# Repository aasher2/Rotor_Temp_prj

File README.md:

# Welcome!

We created this repository in case another team is tasked to bring this project to completion. All necessary documents and many useful links are provided.

To download this entire project as a zipped folder, simply click the "Clone or Download" drop-down to the right of the home page. The option to download as a zipped folder will then be presented. 

This repository is split between paths for firmware and hardware. The firmware path just leads to the final code used for the BLE server and BLE client. The hardware path diverges into paths for the final design and for the proof of concept design. Most of the documents/datasheets/references will be found in the proof of concept folder.

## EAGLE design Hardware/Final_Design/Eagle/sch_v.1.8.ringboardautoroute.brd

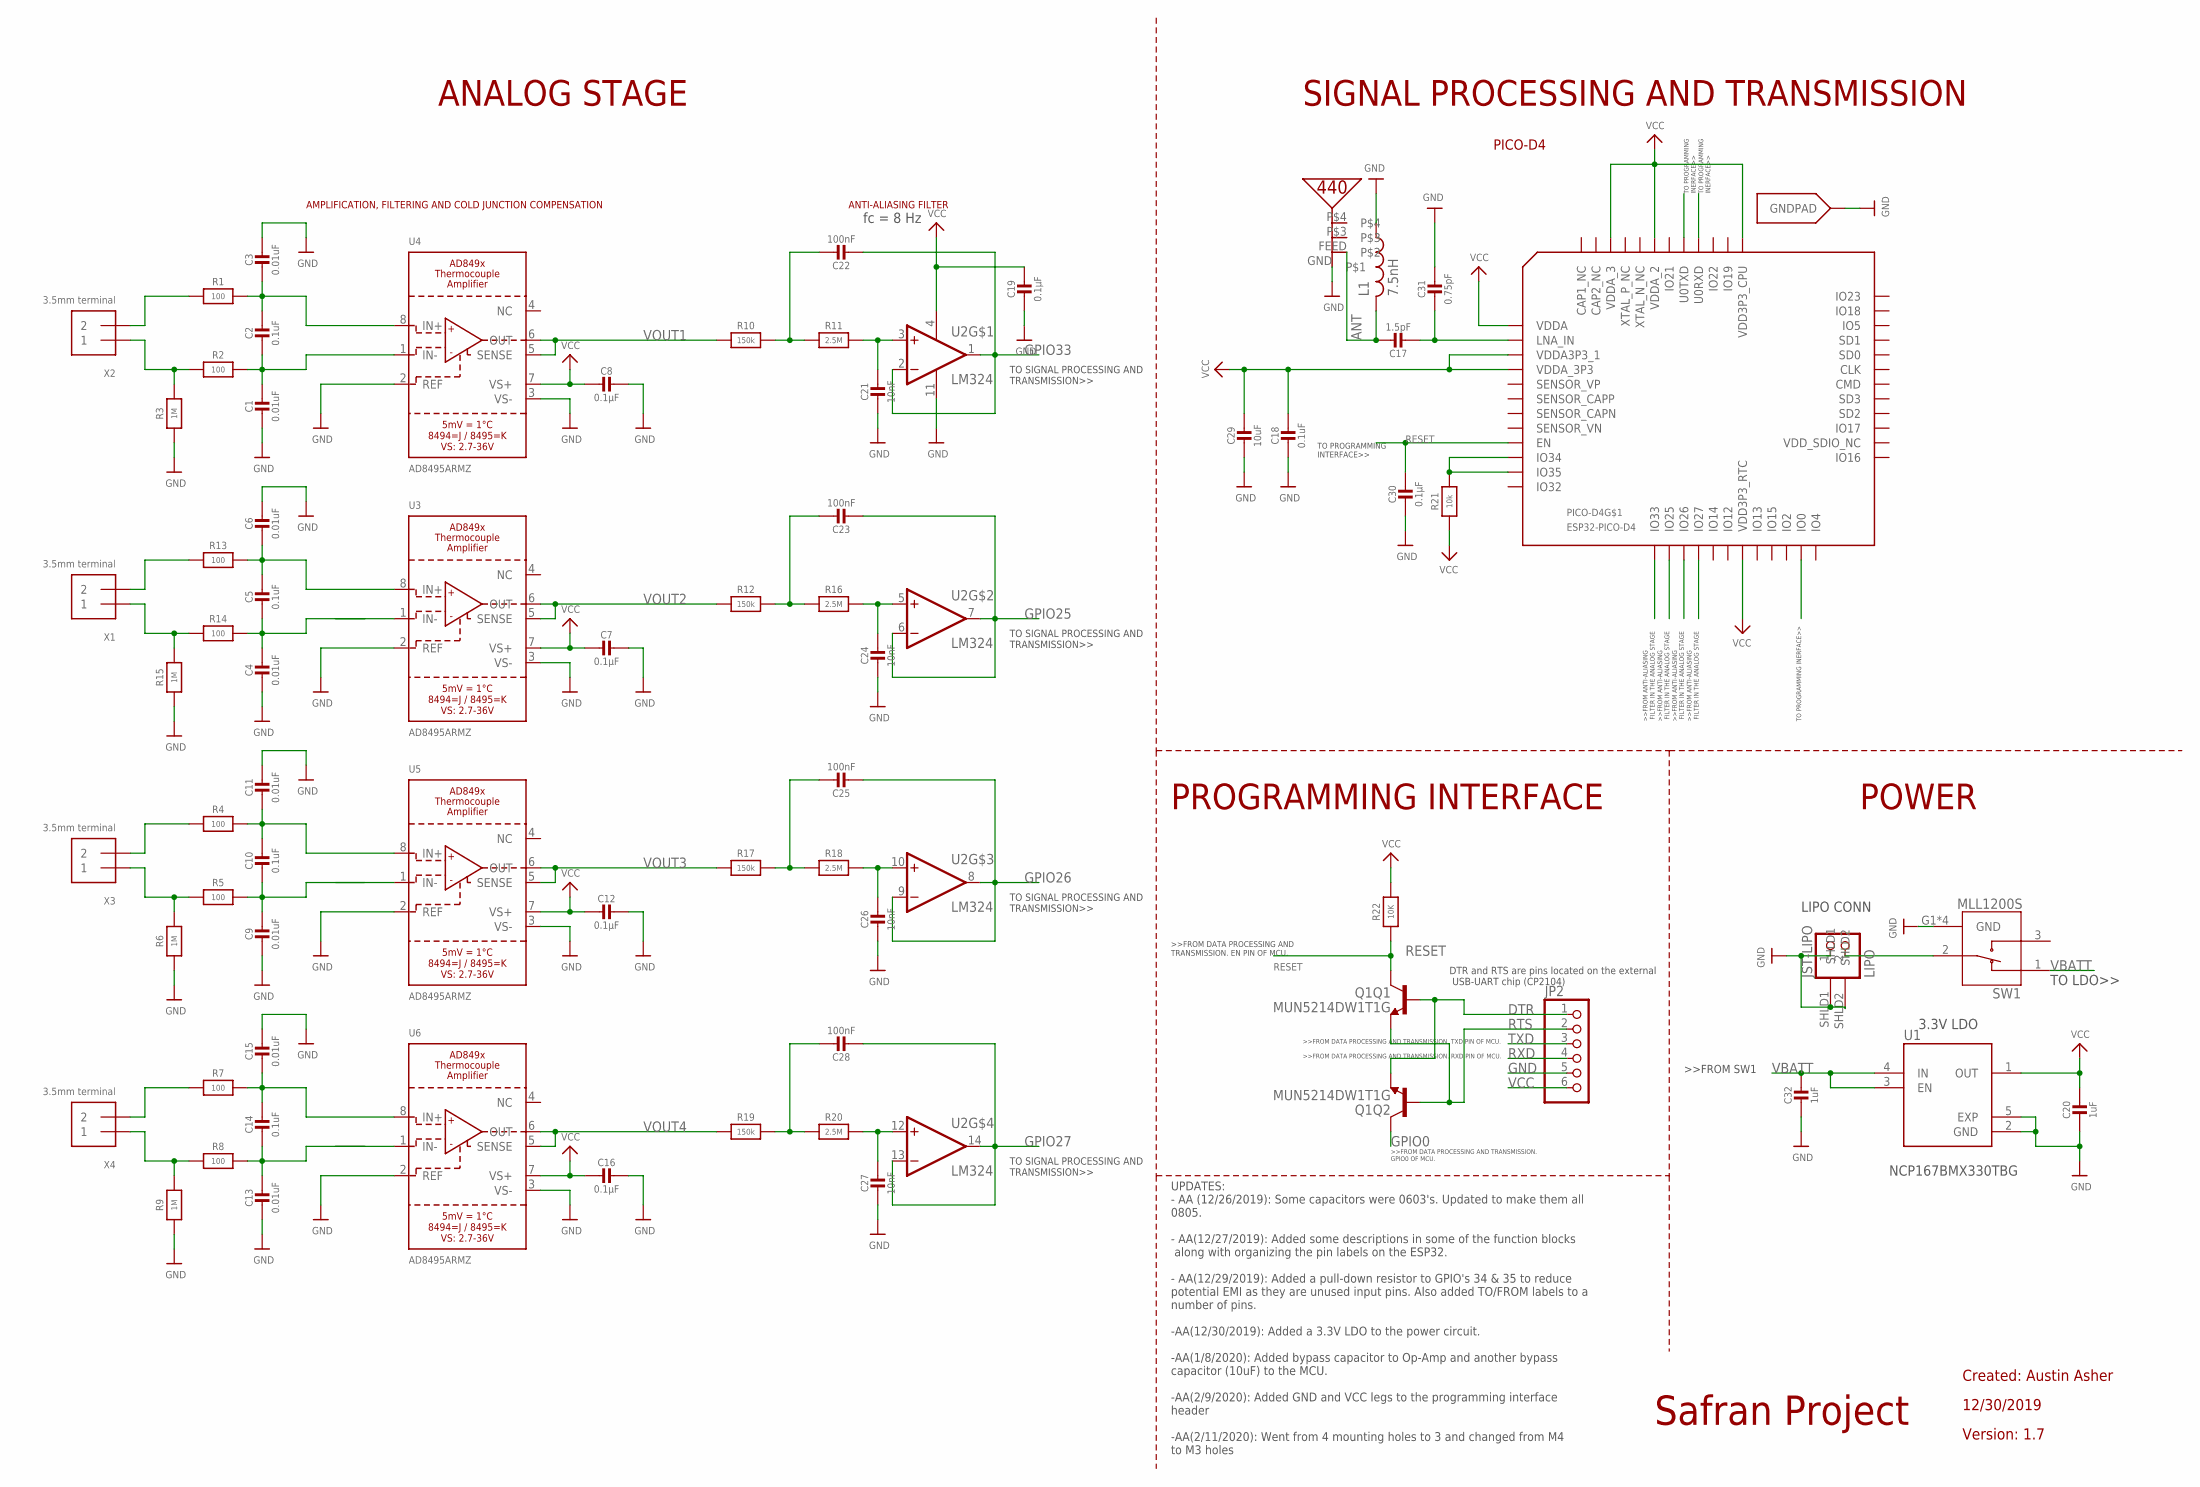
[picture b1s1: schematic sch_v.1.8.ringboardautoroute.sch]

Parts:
C1, C3, C4, C6, C9, C11, C13, C15: 0.01uF; 0805-NO@1
C2, C5, C10, C14, C18: 0.1uF; 0805-NO@1
C7, C8, C12, C16, C19, C30: 0.1µF; 0805-NO@1
C17: 1.5pF; 0805-NO@1
C20, C32: 1uF; 0805-NO@1
C21, C24, C26, C27: 10nF; 0805-NO@1
C22, C23, C25, C28: 100nF; 0805-NO@1
C29: 10uF; 0805-NO@1
C31: 0.75pF; 0805-NO@1
JP2: PINHD-1X6; 1X06
JST-LIPO: LIPO; JSTPH2
L1: 7.5nH; RESC0402_N
PICO-D4: ESP32-PICO-D4; PICO-D4-QFN48
Q1: MUN5214DW1T1G; DUAL_NPN_SC70-6
R1, R2, R4, R5, R7, R8, R13, R14: 100; 0805-NO
R3, R6, R9, R15: 1M; 0805-NO
R10, R12, R17, R19: 150k; 0805-NO
R11, R16, R18, R20: 2.5M; 0805-NO
R21: 10k; 0805-NO
R22: 10K; 0805-NO
SW1: MLL1200S; SW_MLL1200S
U1: NCP170AMX300TCG; VREG_NCP170AMX300TCG
U2: LM324; SOIC127P600X175-14N
U3, U4, U5, U6: AD8495ARMZ; MSOP8_0.65MM
U$35: PRO-OB-440
X1, X2, X3, X4: 3.5mm terminal; TERMBLOCK_1X2-3.5MM

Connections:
ANT: C17.1, L1.2, U$35.FEED
DTR: JP2.1, Q1.1 (E), Q1.5 (B)
GND: C1.2, C3.1, C4.2, C6.1, C7.1, C8.1, C9.2, C11.1, C12.1, C13.2, C15.1, C16.1, C18.2, C19.2, C20.2, C21.2, C24.2, C26.2, C27.2, C29.2, C30.2, C31.1, C32.2, JP2.5, JST-LIPO.1, JST-LIPO.SHLD1, JST-LIPO.SHLD2, L1.1, PICO-D4.EXP (GNDPAD), R3.1, R6.1, R9.1, R15.1, SW1.G1 (GND), SW1.G2 (GND), SW1.G3 (GND), SW1.G4 (GND), U1.2 (GND), U1.5 (EXP), U2.11 (VCC-), U3.2 (REF), U3.3 (VS-), U4.2 (REF), U4.3 (VS-), U5.2 (REF), U5.3 (VS-), U6.2 (REF), U6.3 (VS-), U$35.GND
GPIO0: PICO-D4.23 (IO0), Q1.6 (C)
GPIO25: C23.2, U2.6 (INVERTING_INPUT2), U2.7 (OUTPUT2)
GPIO26: C25.2, U2.8 (OUTPUT3), U2.9 (INVERTING_INPUT3)
GPIO27: C28.2, U2.13 (INVERTING_INPUT4), U2.14 (OUTPUT4)
GPIO33: C22.2, U2.1 (OUTPUT1), U2.2 (INVERTING_INPUT1)
IN+: R13.1, X1.2
IN+1: R1.1, X2.2
IN+2: R4.1, X3.2
IN+3: R7.1, X4.2
IN-: R14.1, R15.2, X1.1
IN-1: R2.1, R3.2, X2.1
IN-2: R5.1, R6.2, X3.1
IN-3: R8.1, R9.2, X4.1
IO12: PICO-D4.18 (IO12)
IO21: PICO-D4.42 (IO21)
LNA_IN: C17.2, C31.2, PICO-D4.2 (LNA_IN)
unnamed: C2.1, C3.2, R1.2, U4.8 (IN+)
unnamed: C5.1, C6.2, R13.2, U3.8 (IN+)
unnamed: C4.1, C5.2, R14.2
unnamed: C1.1, C2.2, R2.2, U4.1 (IN-)
unnamed: C10.1, C11.2, R4.2, U5.8 (IN+)
unnamed: C9.1, C10.2, R5.2
unnamed: C14.1, C15.2, R7.2, U6.8 (IN+)
unnamed: C13.1, C14.2, R8.2
unnamed: JST-LIPO.2, SW1.2
unnamed: C22.1, R10.2, R11.1
unnamed: C21.1, R11.2, U2.3 (NON-INVERTING_INPUT1)
unnamed: C24.1, R16.2, U2.5 (NON-INVERTING_INPUT2)
unnamed: C23.1, R12.2, R16.1
unnamed: C25.1, R17.2, R18.1
unnamed: C28.1, R19.2, R20.1
unnamed: C26.1, R18.2, U2.10 (NON-INVERTING_INPUT3)
unnamed: C27.1, R20.2, U2.12 (NON-INVERTING_INPUT4)
unnamed: PICO-D4.10 (IO34), PICO-D4.11 (IO35), R21.2
RESET: C30.1, PICO-D4.9 (EN), Q1.3 (C), R22.1
RTS: JP2.2, Q1.2 (B), Q1.4 (E)
RXD: JP2.4, PICO-D4.40 (U0RXD)
SENSOR_CAPN: PICO-D4.7 (SENSOR_CAPN)
TXD: JP2.3, PICO-D4.41 (U0TXD)
VBATT: C32.1, SW1.1, U1.3 (EN), U1.4 (IN)
VCC: C7.2, C8.2, C12.2, C16.2, C18.1, C19.1, C20.1, C29.1, JP2.6, PICO-D4.1 (VDDA), PICO-D4.3 (VDDA3P3_1), PICO-D4.4 (VDDA_3P3), PICO-D4.19 (VDD3P3_RTC), PICO-D4.37 (VDD3P3_CPU), PICO-D4.43 (VDDA_2), PICO-D4.46 (VDDA_3), R21.1, R22.2, U1.1 (OUT), U2.4 (VCC+), U3.7 (VS+), U4.7 (VS+), U5.7 (VS+), U6.7 (VS+)
VOUT1: R10.1, U4.5 (SENSE), U4.6 (OUT)
VOUT2: R12.1, U3.5 (SENSE), U3.6 (OUT)
VOUT3: R17.1, U5.5 (SENSE), U5.6 (OUT)
VOUT4: R19.1, U6.5 (SENSE), U6.6 (OUT)

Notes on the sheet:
LIPO CONN
Created: Austin Asher
Safran Project
12/30/2019
Version: 1.7
PICO-D4
ANALOG STAGE
PROGRAMMING INTERFACE
POWER
SIGNAL PROCESSING AND TRANSMISSION
UPDATES: - AA (12/26/2019): Some capacitors were 0603's. Updated to make them all 0805. - AA(12/27/2019): Added some descriptions in some of the function blocks along with organizing the pin labels on the ESP32. - AA(12/29/2019): Added a pull-down resistor to GPIO's 34 & 35 to reduce potential EMI 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
DTR and RTS are pins located on the external USB-UART chip (CP2104)
AMPLIFICATION, FILTERING AND COLD JUNCTION COMPENSATION
ANTI-ALIASING FILTER
TO SIGNAL PROCESSING AND TRANSMISSION>>
TO PROGRAMMING INERFACE>>
TO PROGRAMMING INTERFACE>>
TO PROGRAMMING INERFACE>>
NCP167BMX330TBG
TO LDO>>
3.3V LDO
fc = 8 Hz

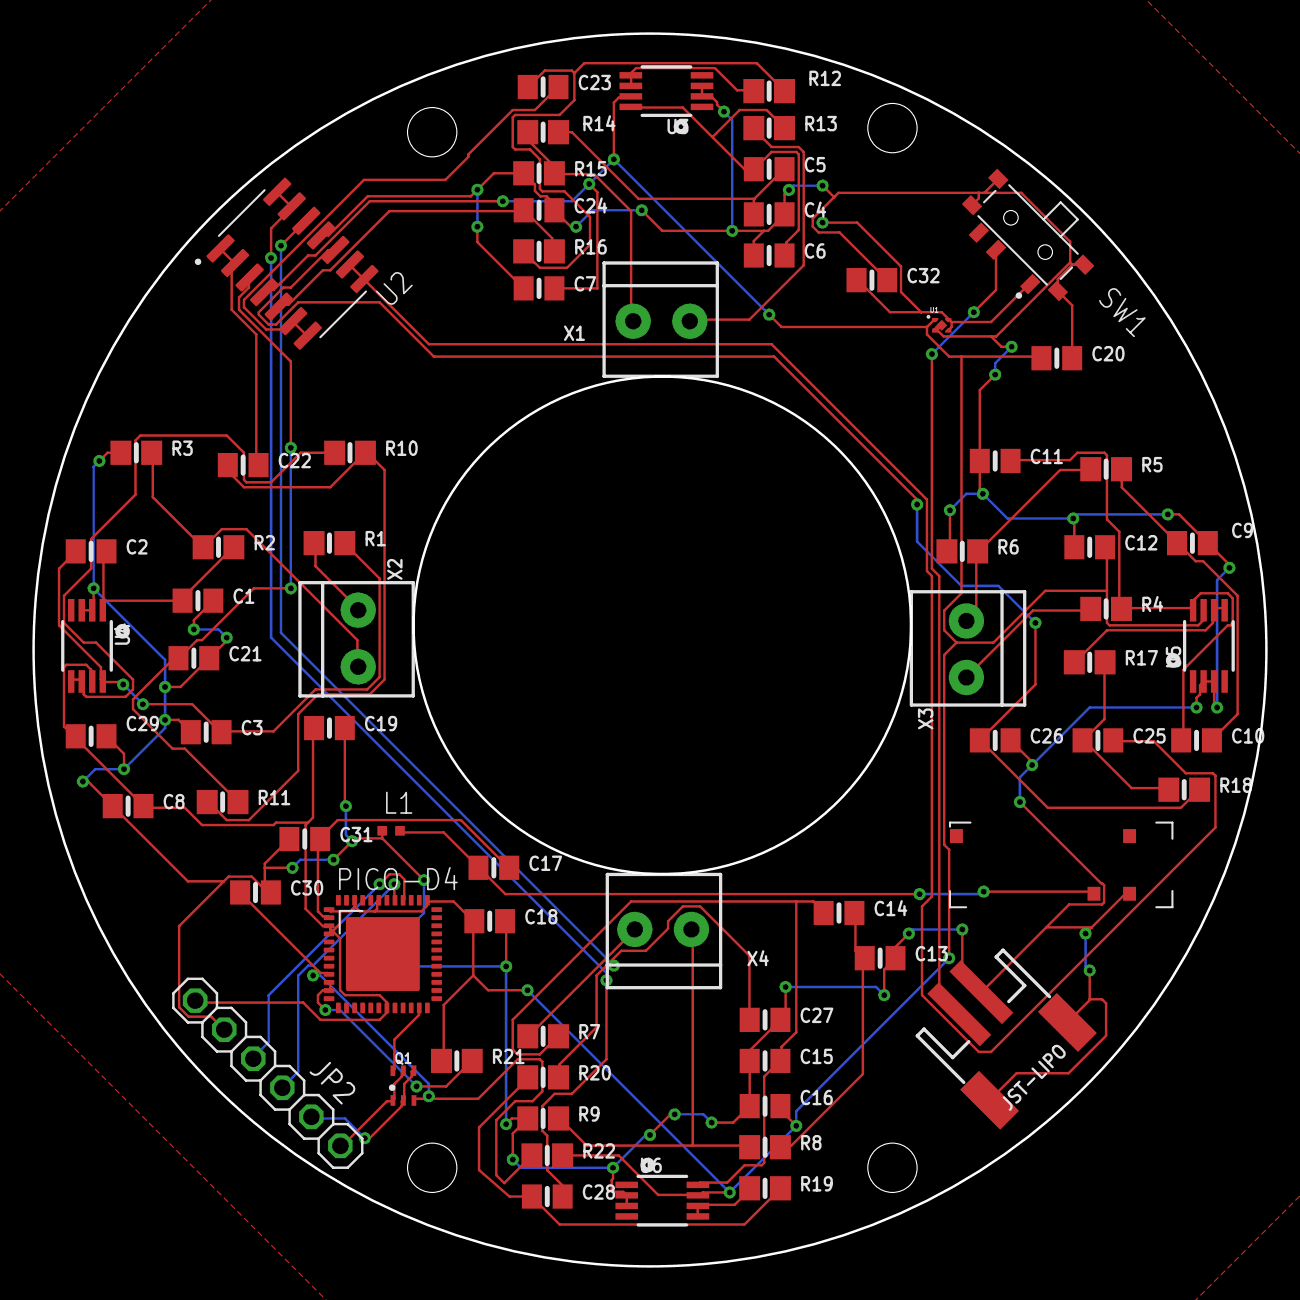
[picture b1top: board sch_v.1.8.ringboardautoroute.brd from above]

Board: 2 copper layers, 76.2 x 76.2 mm, 71 parts (0 on the bottom side), 45 nets.

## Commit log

2020-04-25 Create Useful Links
2020-04-25 Update Useful Links
2020-04-25 Rename Useful Links to Useful Links.md
2020-04-26 Create BOM
2020-04-26 Create Server
2020-04-26 Create Proof_of_Concept
2020-04-26 Create Final_Design
2020-04-26 Create Test
2020-04-26 Create t
2020-04-27 Create AD8495 Docs

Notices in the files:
parts and their libraries:
microbuilder: This work is placed in the public domain, and may be freely used for commercial and non-commercial work with the following conditions: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
